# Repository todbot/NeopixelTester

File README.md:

# NeopixelTester

Some testing hardware for Neopixels (WS2812, SK6812)

In this repo:
- boards - schematic in Eagle format
- sketches - Sketches to run on Trinket M0

## Video of how it works
Click the pic to watch the video

## PCBs

Boards available on OSHPark:
https://oshpark.com/shared_projects/BqFE6DLx

Or you can mill your own with an Othermill/Bantam tools PCB mill. The board is designed to be single-sided milled with only three straight jumpers.

## Bill of Materials
Bill of materials:
- Adafruit Trinket M0
- Adafruit 35mm slide pots x 3
- 74AHCT1G125DBV or SN74LV1T125DCKR level-shifter in SOT23-5 package
- 500 ohm resistor in 0603 package
- tact switch button
- male header pins, cut to length
- female header sockets, cut to length

Or if you're interested in the [60mm Amazon faders](http://amzn.com/B07PNDLKQQ?tag=todbotblog-20) on the other board.
And here's the [USB power meter](http://amzn.com/B07DK6FT4Q?tag=todbotblog-20) I showed in the video.

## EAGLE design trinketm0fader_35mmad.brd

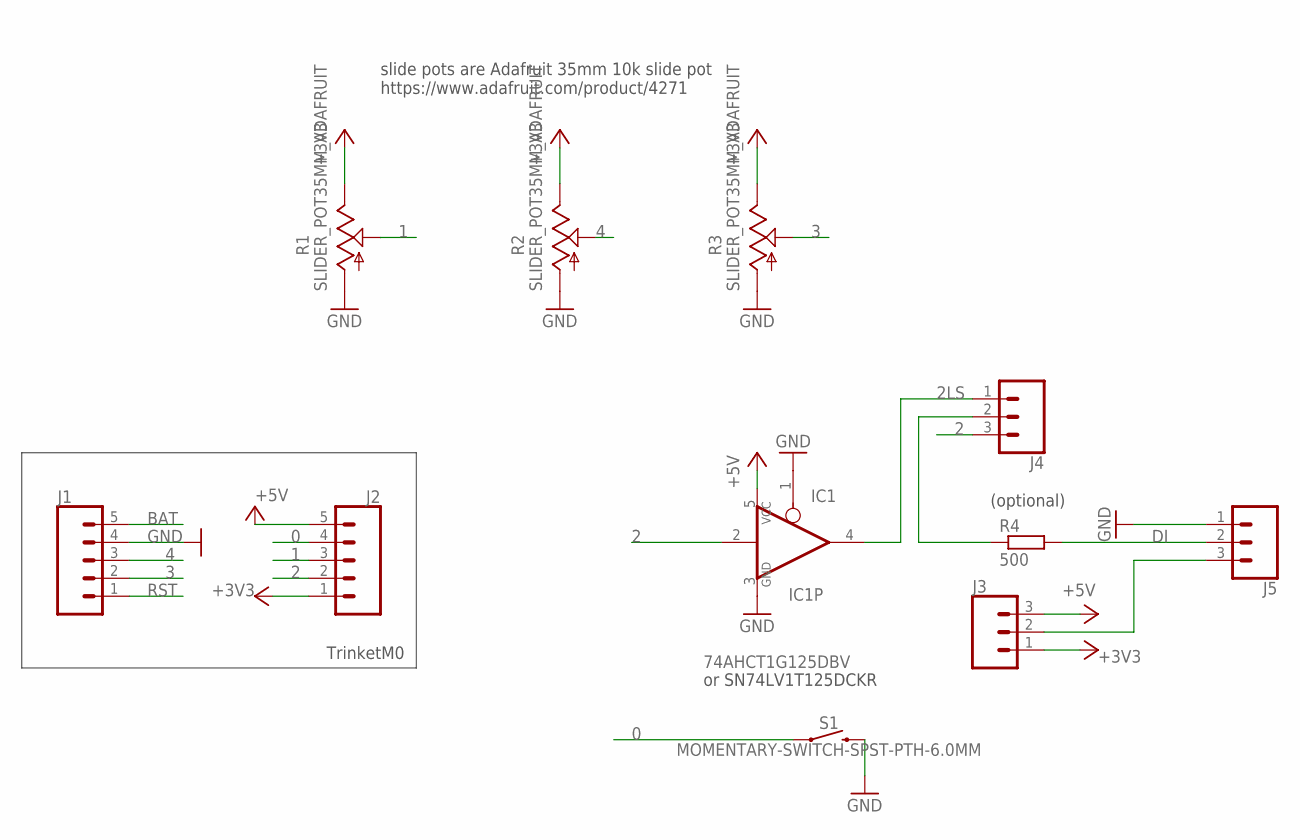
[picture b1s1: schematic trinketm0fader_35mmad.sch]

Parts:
IC1: 74AHCT1G125DBV; SOT23-5
J1, J2: CONN_05; 1X05
J3, J4, J5: CONN_03; 1X03
R1, R2, R3: SLIDER_POT35MM_ADAFRUIT; SLIDEPOD_35MM_ADAFRUIT
R4: 500; R0603
S1: MOMENTARY-SWITCH-SPST-PTH-6.0MM; TACTILE_SWITCH_PTH_6.0MM

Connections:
0: J2.4, S1.1
1: J2.3, R1.P$2 (W)
2: IC1.2 (I), J2.2, J4.3
2LS: IC1.4 (O), J4.1
3: J1.2, R3.P$2 (W)
4: J1.3, R2.P$2 (W)
+3V3: J2.1, J3.1, R1.P$1 (V), R2.P$1 (V), R3.P$1 (V)
+5V: IC1.5 (VCC), J2.5, J3.3
BAT: J1.5
DI: J5.2, R4.2
GND: IC1.1 (OE), IC1.3 (GND), J1.4, J5.1, R1.P$3 (G), R2.P$3 (G), R3.P$3 (G), S1.3 (2)
unnamed: J3.2, J5.3
unnamed: J4.2, R4.1
RST: J1.1

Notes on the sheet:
(optional)
TrinketM0
slide pots are Adafruit 35mm 10k slide pot https://www.adafruit.com/product/4271
or SN74LV1T125DCKR

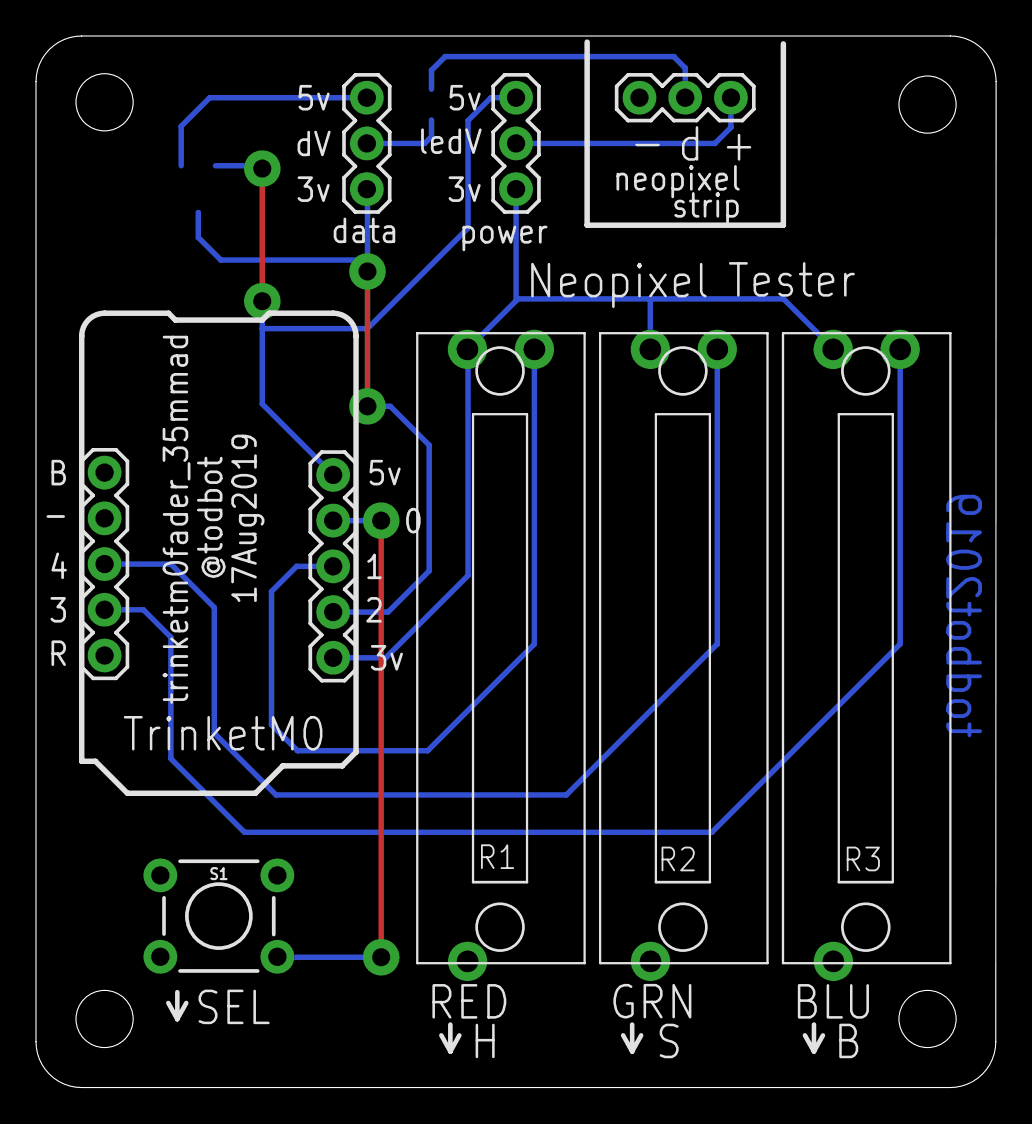
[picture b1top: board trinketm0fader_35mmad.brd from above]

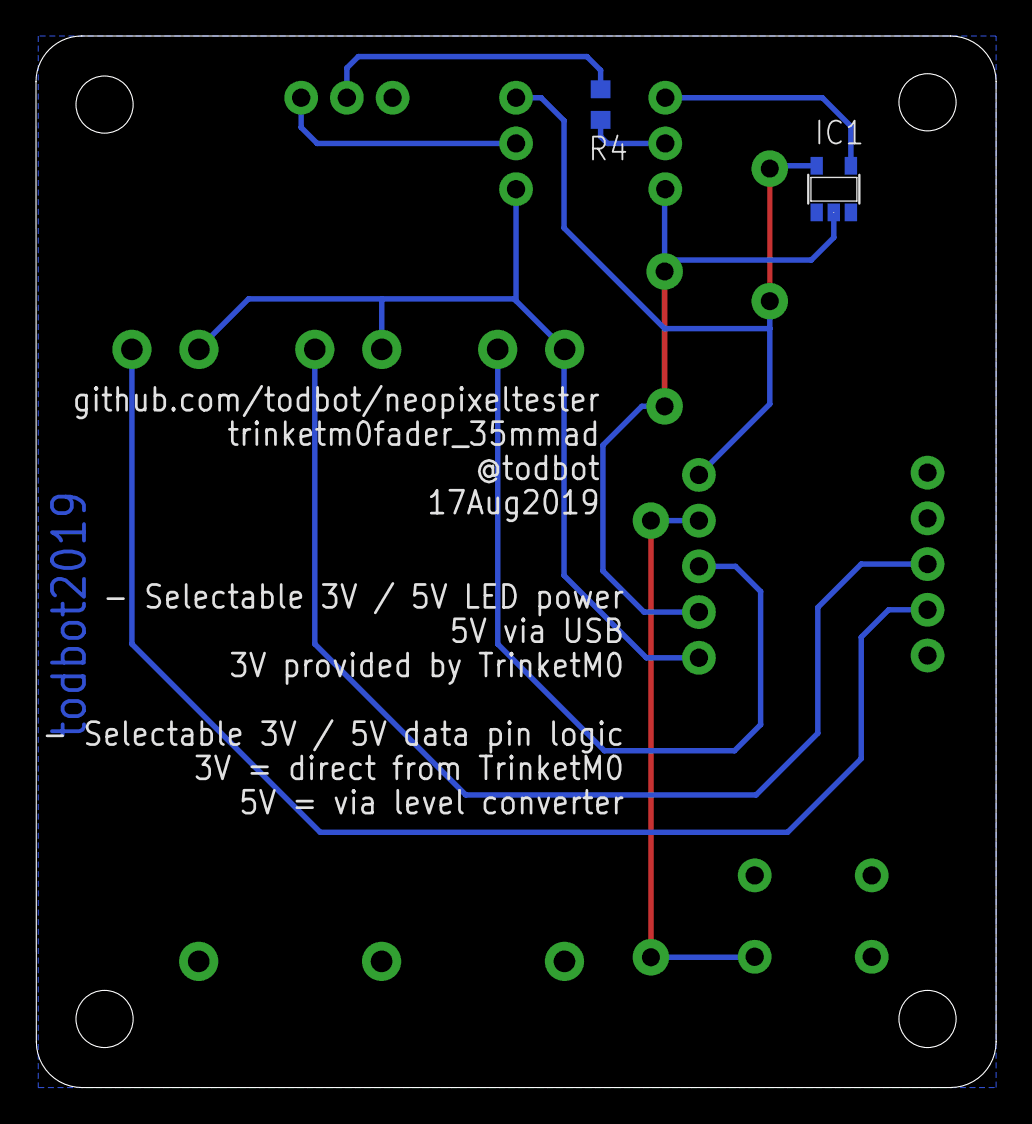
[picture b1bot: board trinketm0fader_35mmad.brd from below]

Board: 2 copper layers, 53.3 x 58.4 mm, 11 parts (2 on the bottom side), 12 nets.

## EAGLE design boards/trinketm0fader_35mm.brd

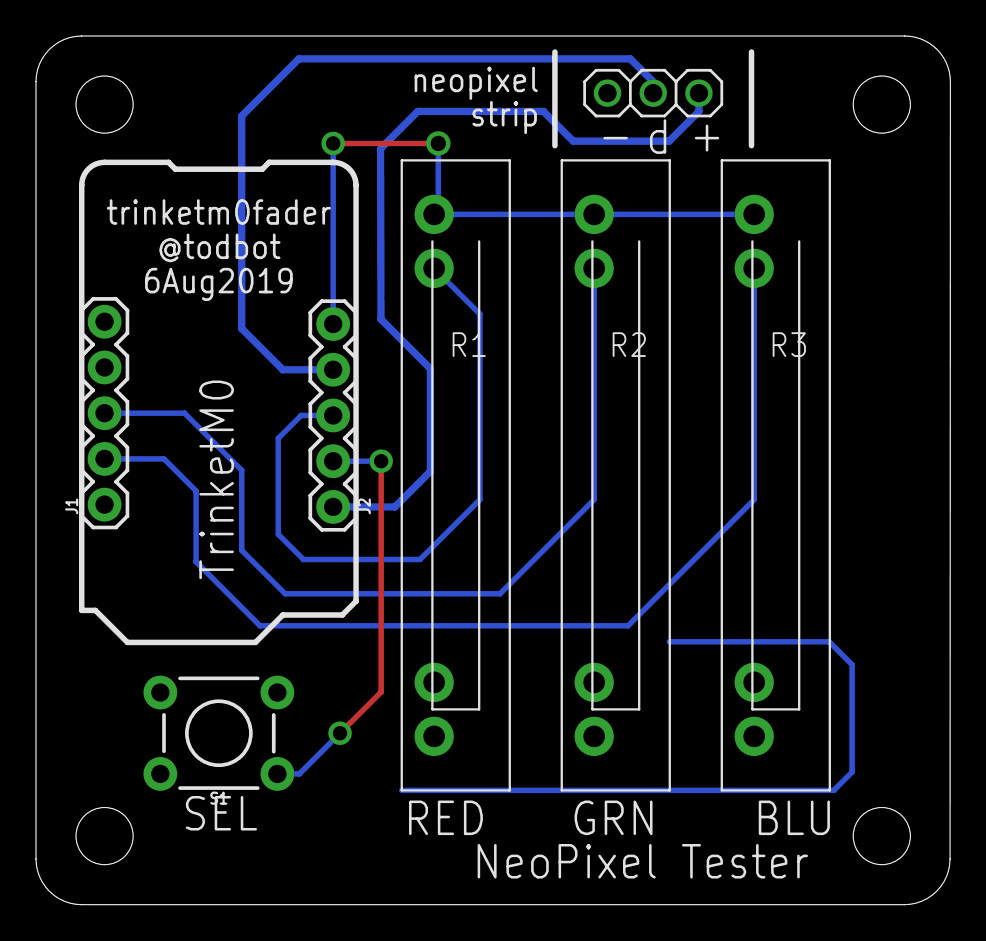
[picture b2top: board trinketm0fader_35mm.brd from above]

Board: 2 copper layers, 50.8 x 48.3 mm, 7 parts (0 on the bottom side), 8 nets.

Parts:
J1, J2: 1X05
JP1: 1X03
R1, R2, R3: SLIDER_POT; SLIDEPOT_35MM_GUITAR
S1: MOMENTARY-SWITCH-SPST-PTH-6.0MM; TACTILE_SWITCH_PTH_6.0MM

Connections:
0: J2.2, S1.1
1: J2.3, R1.P$2
2: J2.4, JP1.2
3: J1.2, R3.P$2
4: J1.3, R2.P$2
+3V3: J2.5, R1.P$1, R2.P$1, R3.P$1
+5V: J2.1, JP1.3
GND: J1.4, JP1.1, R1.P$4, R2.P$4, R3.P$4, S1.3

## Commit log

2019-08-14 cleanup
2019-08-19 added adafruit fader version
2019-08-21 oops
2019-08-22 reorg
2019-08-22 docs
2019-08-22 quicky bom
2019-08-22 more docs

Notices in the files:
parts and their libraries:
SparkFun-Connectors: Licensing: Creative Commons ShareAlike 4.0 International - https://creativecommons.org/licenses/by-sa/4.0
